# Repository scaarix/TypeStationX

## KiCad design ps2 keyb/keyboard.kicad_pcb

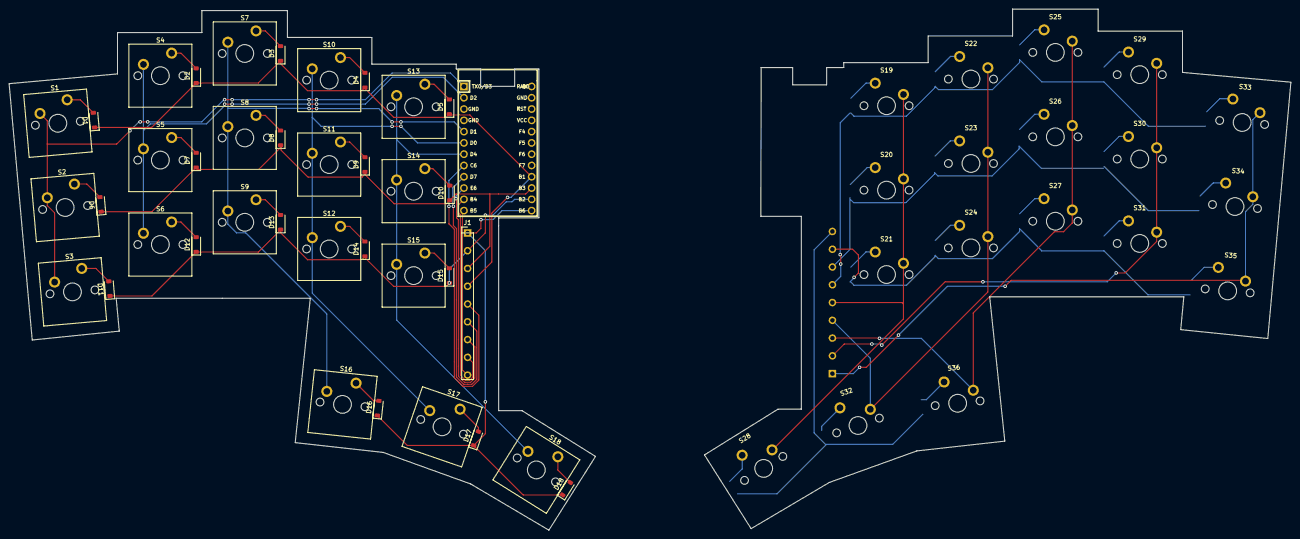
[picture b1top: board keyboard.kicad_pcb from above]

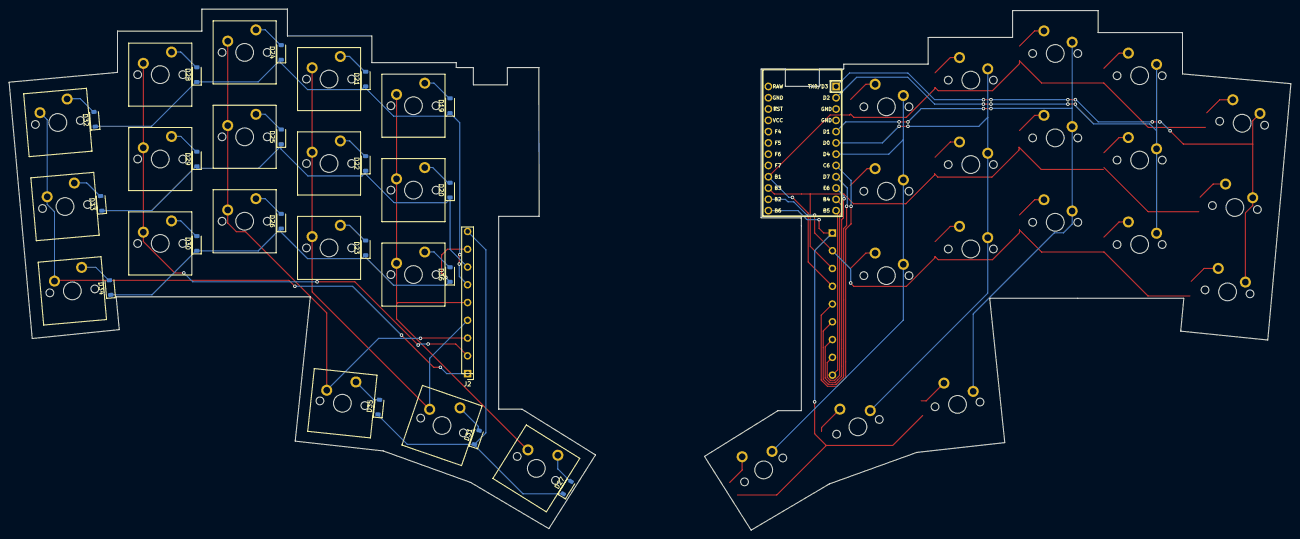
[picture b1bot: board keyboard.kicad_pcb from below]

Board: 2 copper layers, 288.5 x 117.3 mm, 75 parts (37 on the bottom side), 50 nets.

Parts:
D1, D2, D3, D4, D5, D6, D7, D8, D9, D10, D11, D12, D13, D14, D15, D16, D17, D18, D19, D20, D21, D22, D23, D24, D25, D26, D27, D28, D29, D30, D31, D32, D33, D34, D35, D36: D_Small; D_SOD-123
J1, J2: Conn_01x09; 1x9 4mm
S1, S2, S3, S4, S5, S6, S7, S8, S9, S10, S11, S12, S13, S14, S15, S16, S17, S18, S19, S20, S21, S22, S23, S24, S25, S26, S27, S28, S29, S30, S31, S32, S33, S34, S35, S36: SW_Push; SW_Cherry_MX_PCB_1.00u
U2: ProMicro; ArduinoProMicro

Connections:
C1: S1.1, S2.1, S3.1, U2.1 (TX0/PD3)
C2: S4.1, S5.1, S6.1, U2.2 (RX1/PD2)
C3: S7.1, S8.1, S9.1, S16.1, U2.5 (2/PD1)
C4: S10.1, S11.1, S12.1, S17.1, U2.6 (3/PD0)
C5: S13.1, S14.1, S15.1, S18.1, U2.7 (4/PD4)
C6: J1.5, J2.5, S19.1, S20.1, S21.1, S28.1, U2.8 (5/PC6)
C7: J1.6, J2.4, S22.1, S23.1, S24.1, S32.1, U2.9 (6/PD7)
C8: J1.7, J2.3, S25.1, S26.1, S27.1, S36.1, U2.10 (7/PE6)
C9: J1.8, J2.2, S29.1, S30.1, S31.1, U2.11 (8/PB4)
C10: J1.9, J2.1, S33.1, S34.1, S35.1, U2.12 (9/PB5)
unnamed: D1.2 (A), S1.2
unnamed: D2.2 (A), S4.2
unnamed: D3.2 (A), S7.2
unnamed: D4.2 (A), S10.2
unnamed: D5.2 (A), S13.2
unnamed: D6.2 (A), S2.2
unnamed: D7.2 (A), S5.2
unnamed: D8.2 (A), S8.2
unnamed: D9.2 (A), S11.2
unnamed: D10.2 (A), S14.2
unnamed: D11.2 (A), S3.2
unnamed: D12.2 (A), S6.2
unnamed: D13.2 (A), S9.2
unnamed: D14.2 (A), S12.2
unnamed: D15.2 (A), S15.2
unnamed: D16.2 (A), S16.2
unnamed: D17.2 (A), S17.2
unnamed: D18.2 (A), S18.2
unnamed: D19.2 (A), S19.2
unnamed: D20.2 (A), S20.2
unnamed: D21.2 (A), S22.2
unnamed: D22.2 (A), S23.2
unnamed: D23.2 (A), S24.2
unnamed: D24.2 (A), S25.2
unnamed: D25.2 (A), S26.2
unnamed: D26.2 (A), S27.2
unnamed: D27.2 (A), S28.2
unnamed: D28.2 (A), S29.2
unnamed: D29.2 (A), S30.2
unnamed: D30.2 (A), S31.2
unnamed: D31.2 (A), S32.2
unnamed: D32.2 (A), S33.2
unnamed: D33.2 (A), S34.2
unnamed: D34.2 (A), S35.2
unnamed: D35.2 (A), S36.2
unnamed: D36.2 (A), S21.2
R1: D16.1 (K), D17.1 (K), D18.1 (K), D27.1 (K), D31.1 (K), D35.1 (K), J1.1, J2.9, U2.13 (10/PB6)
R2: D11.1 (K), D12.1 (K), D13.1 (K), D14.1 (K), D15.1 (K), D23.1 (K), D26.1 (K), D30.1 (K), D34.1 (K), D36.1 (K), J1.2, J2.8, U2.14 (16/PB2)
R3: D6.1 (K), D7.1 (K), D8.1 (K), D9.1 (K), D10.1 (K), D20.1 (K), D22.1 (K), D25.1 (K), D29.1 (K), D33.1 (K), J1.3, J2.7, U2.15 (14/PB3)
R4: D1.1 (K), D2.1 (K), D3.1 (K), D4.1 (K), D5.1 (K), D19.1 (K), D21.1 (K), D24.1 (K), D28.1 (K), D32.1 (K), J1.4, J2.6, U2.16 (15/PB1)
